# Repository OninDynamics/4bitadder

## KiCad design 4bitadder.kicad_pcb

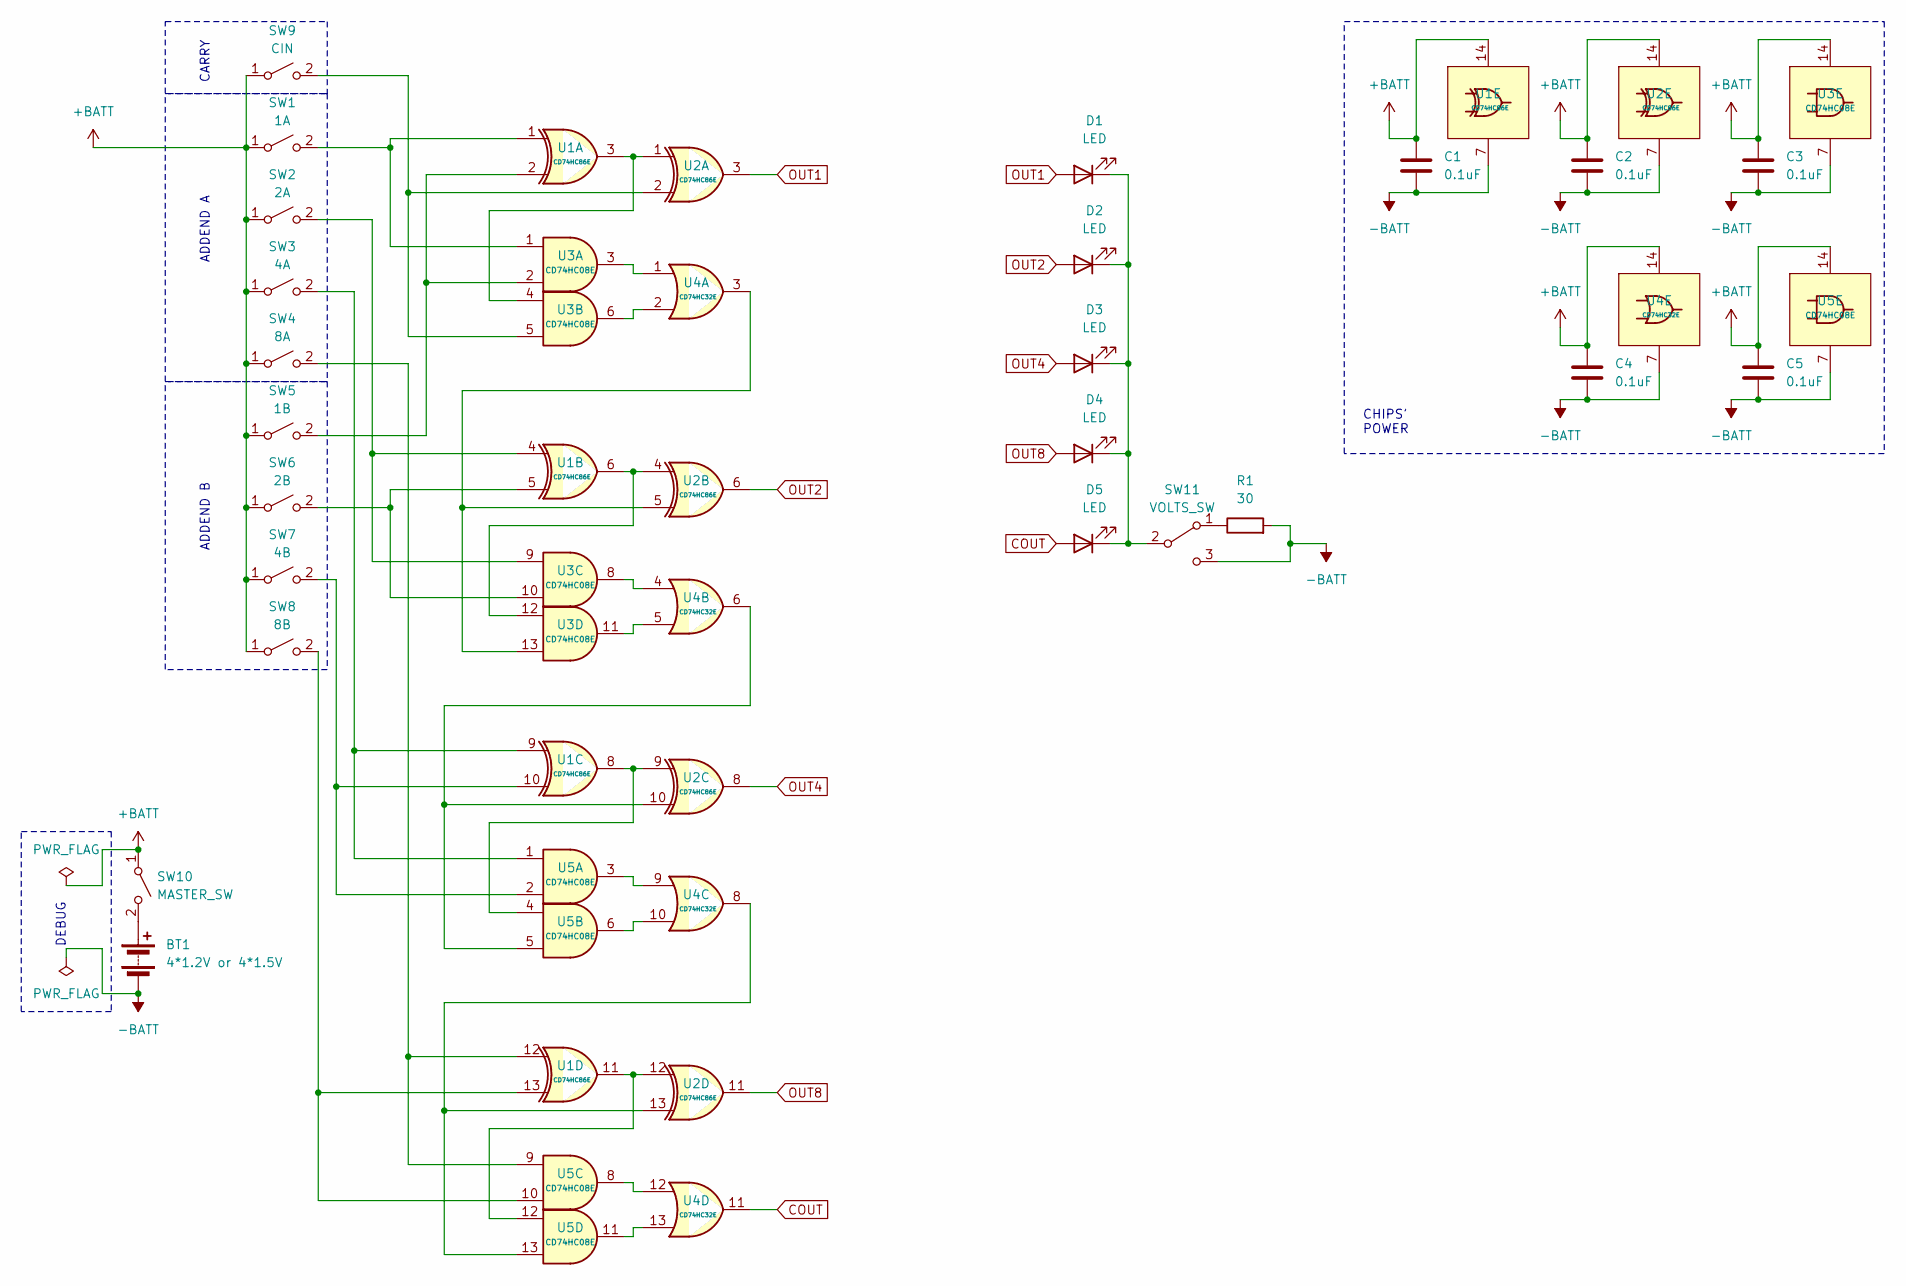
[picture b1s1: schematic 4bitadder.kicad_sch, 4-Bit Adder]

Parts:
BT1: 4*1.2V or 4*1.5V; PAD_Battery Terminal
C1, C2, C3, C4, C5: 0.1uF; C_0805_2012Metric_Pad1.18x1.45mm_HandSolder
D1, D2, D3, D4, D5: LED; LED_WP710A10SURDK5V
R1: 30; R_0805_2012Metric_Pad1.20x1.40mm_HandSolder
SW1: 1A; SW-R2-1A-F-1-0
SW2: 2A; SW-R2-1A-F-1-0
SW3: 4A; SW-R2-1A-F-1-0
SW4: 8A; SW-R2-1A-F-1-0
SW5: 1B; SW-R2-1A-F-1-0
SW6: 2B; SW-R2-1A-F-1-0
SW7: 4B; SW-R2-1A-F-1-0
SW8: 8B; SW-R2-1A-F-1-0
SW9: CIN; SW-R2-1A-F-1-0
SW10: MASTER_SW; SW-R2-1A-F-1-0
SW11: VOLTS_SW; SW_SLW-121586-5A-D
U1, U2: CD74HC86E; DIP-14_W7.62mm_Socket
U3, U5: CD74HC08E; DIP-14_W7.62mm_Socket
U4: CD74HC32E; DIP-14_W7.62mm_Socket

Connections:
+BATT: C1.1, C2.1, C3.1, C4.1, C5.1, SW1.1 (A), SW2.1 (A), SW3.1 (A), SW4.1 (A), SW5.1 (A), SW6.1 (A), SW7.1 (A), SW8.1 (A), SW9.1 (A), SW10.1 (A), U1.14 (VCC), U2.14 (VCC), U3.14 (Vcc), U4.14 (VCC), U5.14 (Vcc)
-BATT: BT1.2 (-), C1.2, C2.2, C3.2, C4.2, C5.2, R1.2, SW11.3 (C), U1.7 (GND), U2.7 (GND), U3.7 (GND), U4.7 (GND), U5.7 (GND)
COUT: D5.2 (A), U4.11 (4Y)
unnamed: BT1.1 (+), SW10.2 (B)
unnamed: D1.1 (K), D2.1 (K), D3.1 (K), D4.1 (K), D5.1 (K), SW11.2 (B)
unnamed: SW1.2 (B), U1.1 (1A), U3.1 (1A)
unnamed: SW2.2 (B), U1.4 (2A), U3.9 (3A)
unnamed: SW3.2 (B), U1.9 (3A), U5.1 (1A)
unnamed: SW4.2 (B), U1.12 (4A), U5.9 (3A)
unnamed: SW5.2 (B), U1.2 (1B), U3.2 (1B)
unnamed: SW6.2 (B), U1.5 (2B), U3.10 (3B)
unnamed: SW7.2 (B), U1.10 (3B), U5.2 (1B)
unnamed: SW8.2 (B), U1.13 (4B), U5.10 (3B)
unnamed: SW9.2 (B), U2.2 (1B), U3.5 (2B)
unnamed: R1.1, SW11.1 (A)
unnamed: U1.3 (1Y), U2.1 (1A), U3.4 (2A)
unnamed: U1.6 (2Y), U2.4 (2A), U3.12 (4A)
unnamed: U1.8 (3Y), U2.9 (3A), U5.4 (2A)
unnamed: U1.11 (4Y), U2.12 (4A), U5.12 (4A)
unnamed: U2.5 (2B), U3.13 (4B), U4.3 (1Y)
unnamed: U2.10 (3B), U4.6 (2Y), U5.5 (2B)
unnamed: U2.13 (4B), U4.8 (3Y), U5.13 (4B)
unnamed: U3.3 (1Y), U4.1 (1A)
unnamed: U3.6 (2Y), U4.2 (1B)
unnamed: U3.8 (3Y), U4.4 (2A)
unnamed: U3.11 (4Y), U4.5 (2B)
unnamed: U4.9 (3A), U5.3 (1Y)
unnamed: U4.10 (3B), U5.6 (2Y)
unnamed: U4.12 (4A), U5.8 (3Y)
unnamed: U4.13 (4B), U5.11 (4Y)
OUT1: D1.2 (A), U2.3 (1Y)
OUT2: D2.2 (A), U2.6 (2Y)
OUT4: D3.2 (A), U2.8 (3Y)
OUT8: D4.2 (A), U2.11 (4Y)

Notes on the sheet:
DEBUG
ADDEND A
CARRY
CHIPS' POWER
ADDEND B

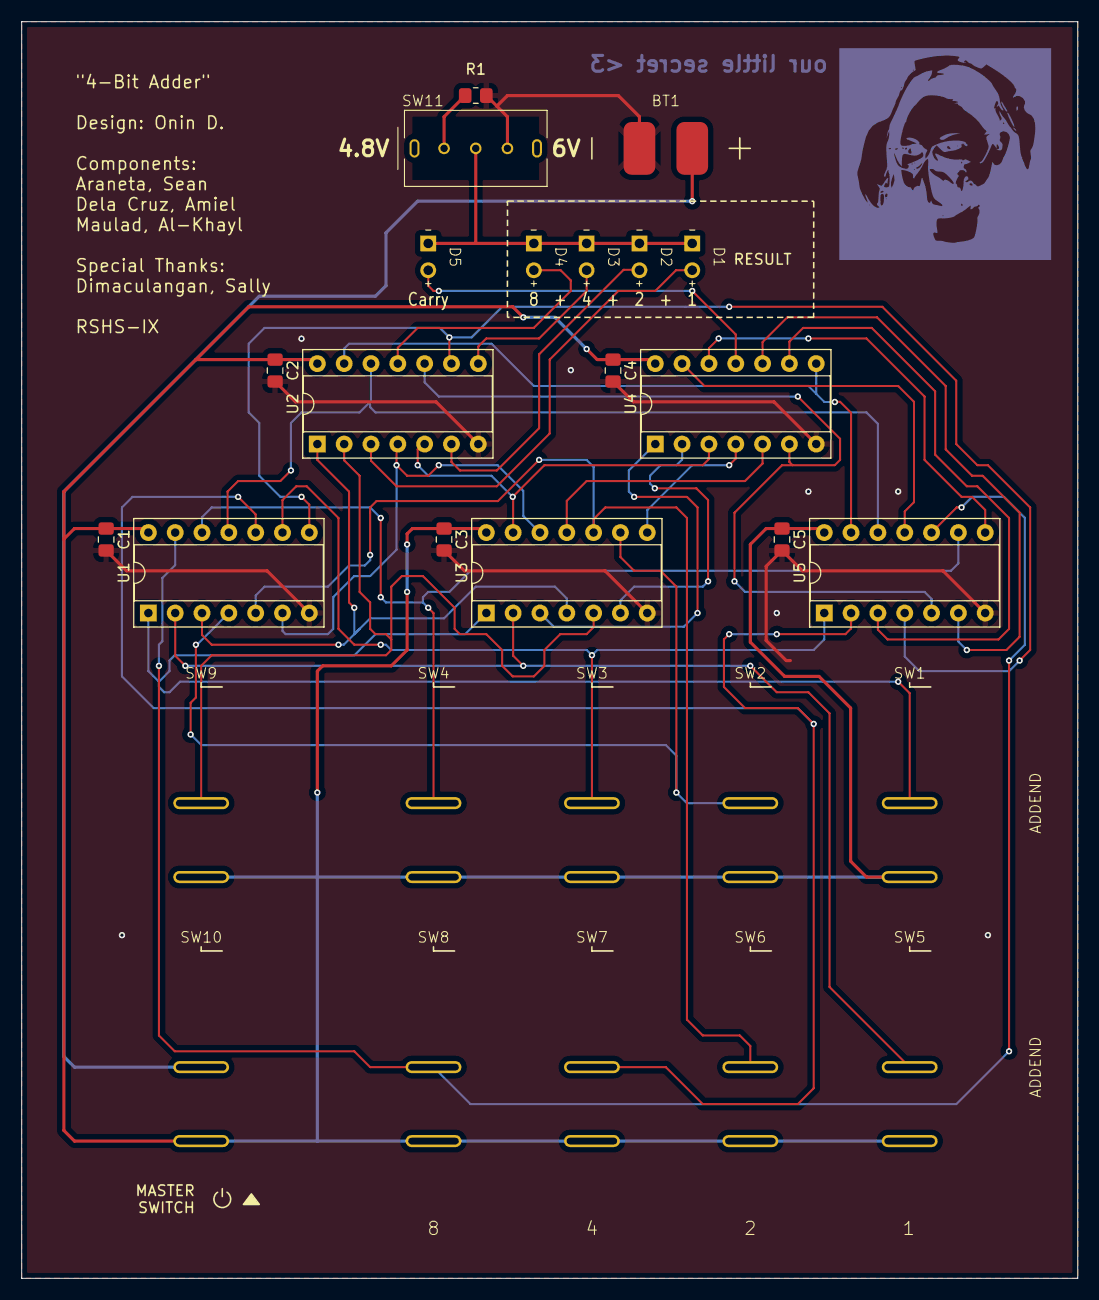
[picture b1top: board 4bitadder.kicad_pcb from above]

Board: 2 copper layers, 100.0 x 119.0 mm, 28 parts (0 on the bottom side), 34 nets.

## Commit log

2023-09-07 Change PCB Colour.
2023-09-10 Repair footprint library. idk what happened there.
2023-09-10 Finalise credits.
2023-09-11 Fix some more files.
2023-09-15 Change switch design. Unroute all vias.
2023-10-09 Add docs. Revise PCB.
